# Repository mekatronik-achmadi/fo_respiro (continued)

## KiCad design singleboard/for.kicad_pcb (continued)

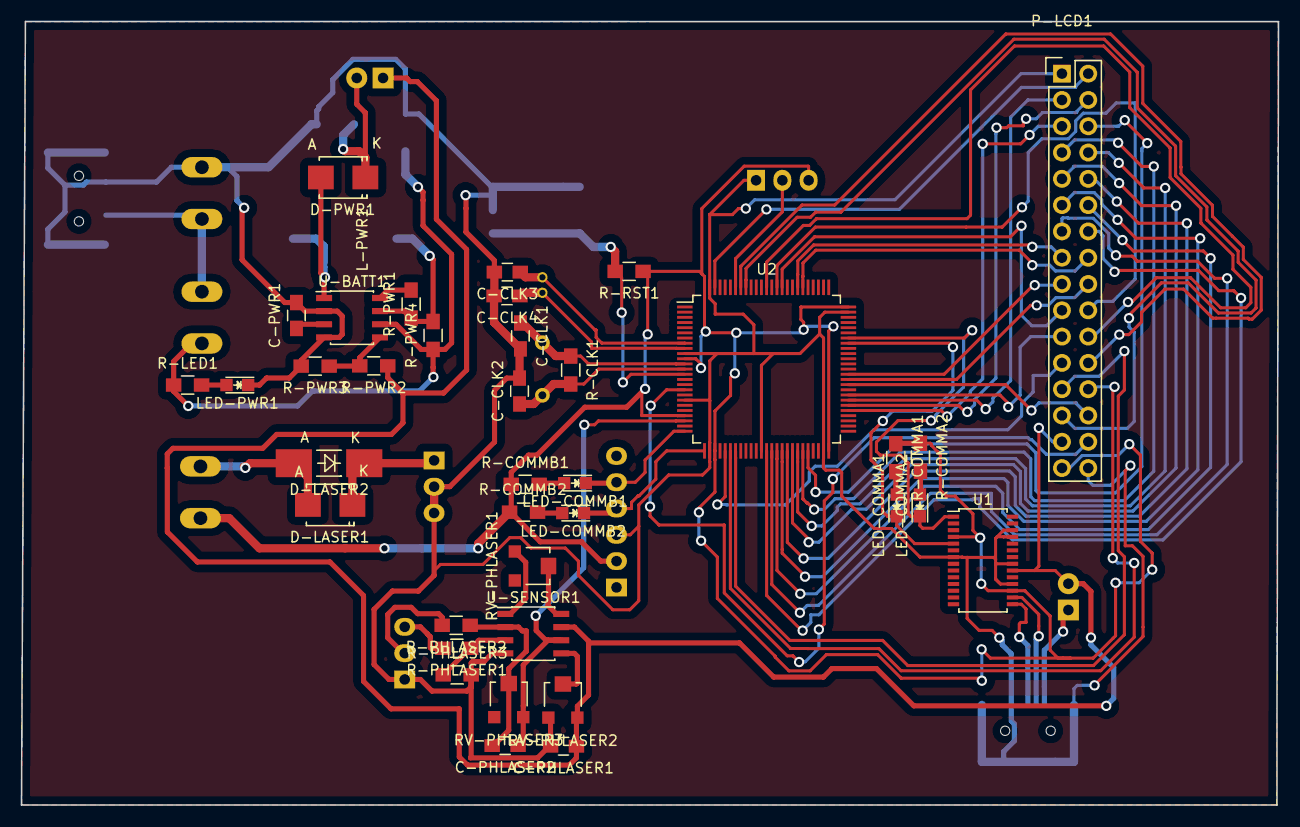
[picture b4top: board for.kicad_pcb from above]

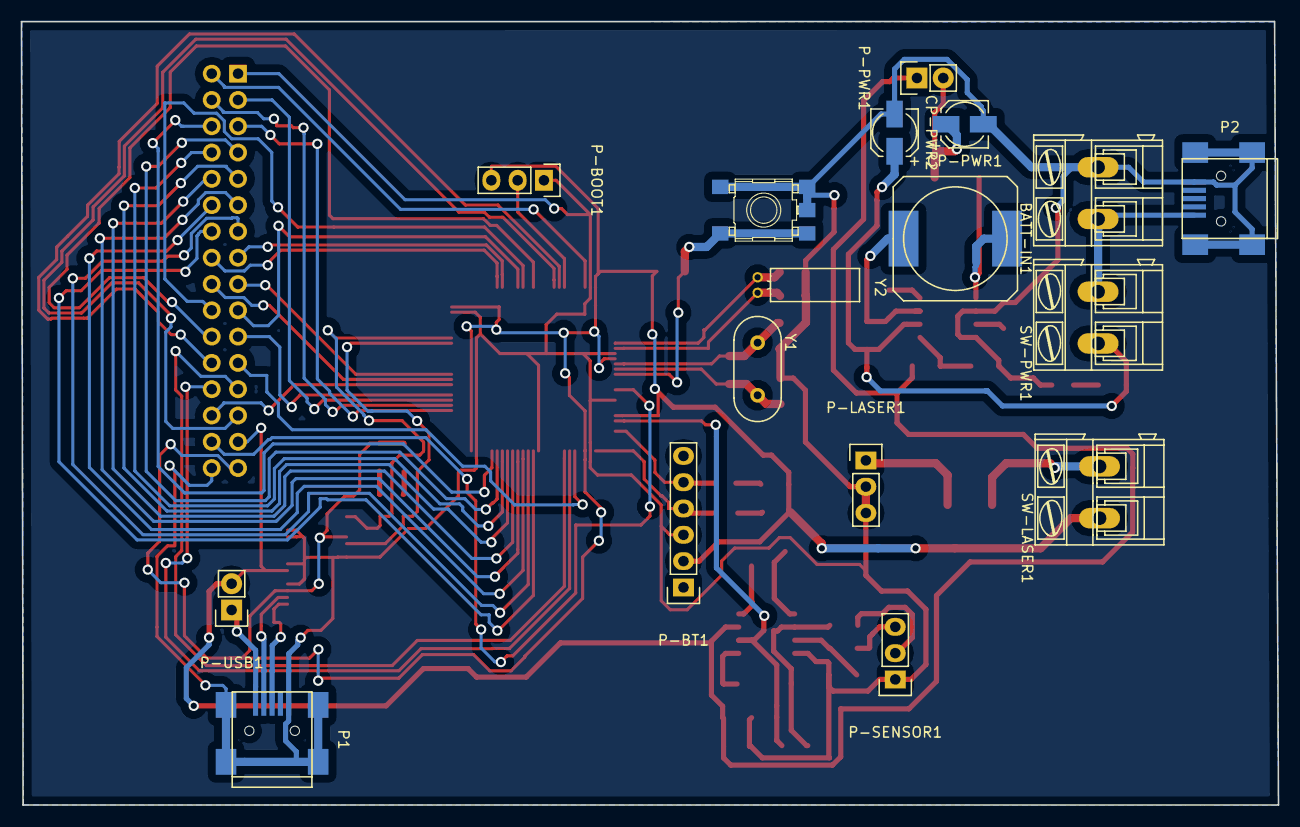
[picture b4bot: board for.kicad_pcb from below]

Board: 2 copper layers, 121.4 x 75.7 mm, 54 parts (17 on the bottom side), 67 nets.

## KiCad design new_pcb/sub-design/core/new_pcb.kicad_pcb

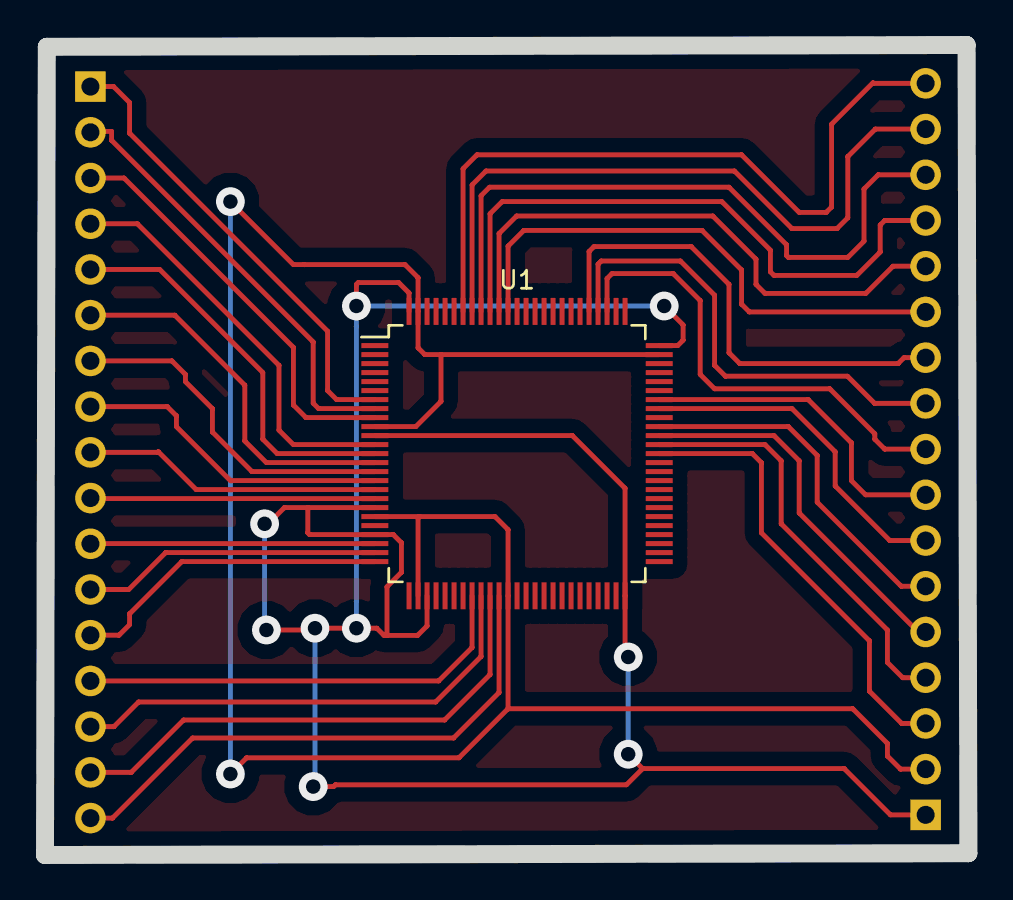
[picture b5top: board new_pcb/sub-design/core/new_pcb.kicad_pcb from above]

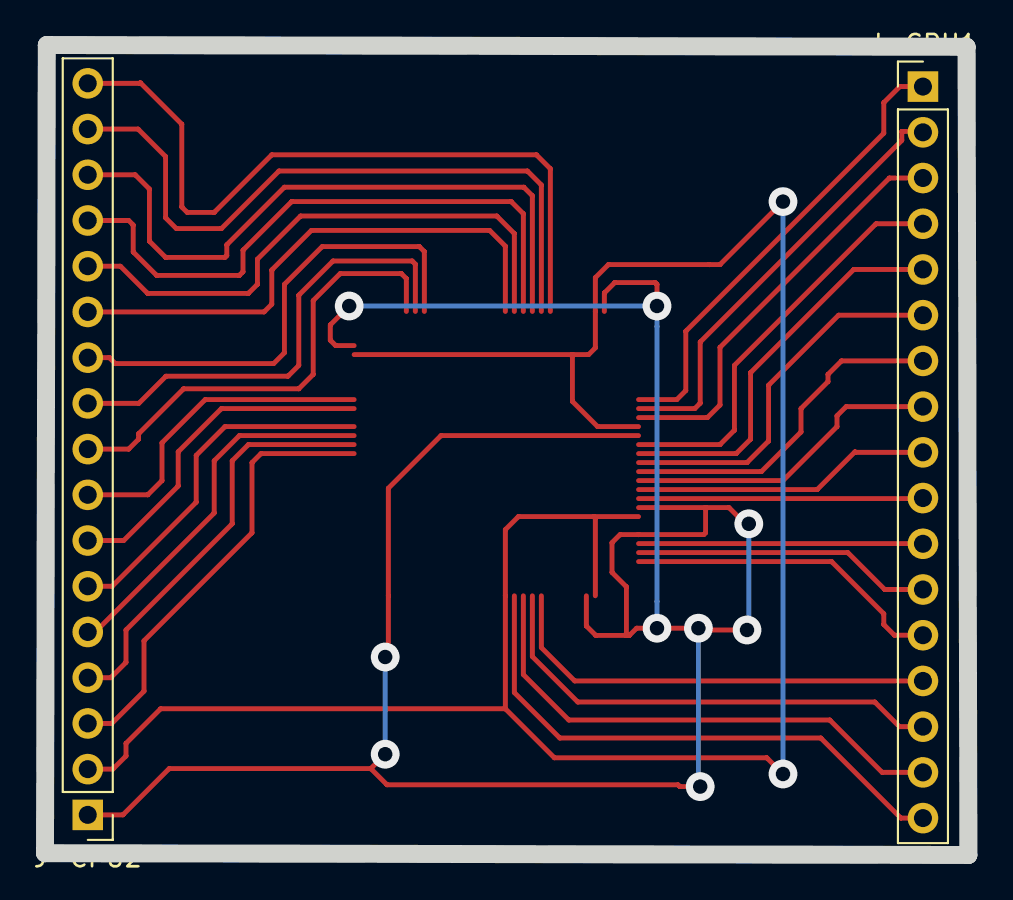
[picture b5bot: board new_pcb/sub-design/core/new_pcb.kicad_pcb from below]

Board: 2 copper layers, 51.3 x 45.0 mm, 3 parts (2 on the bottom side), 34 nets.

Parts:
J-CPU1, J-CPU2: CONN_01X17; Pin_Header_Straight_1x17_Pitch2.54mm
U1: STM32F407VGTx; LQFP-100_14x14mm_Pitch0.5mm

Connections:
/ADC_0: J-CPU1.11, U1.23
/ADC_1: J-CPU1.12, U1.24
/ADC_2: J-CPU1.13, U1.25
/ADC_EOC: J-CPU2.14, U1.91
/ADC_MCLK: J-CPU2.12, U1.89
/ADC_SCL: J-CPU2.15, U1.92
/ADC_SDA: J-CPU2.16, U1.93
/ADC_XCLR: J-CPU2.13, U1.90
/BOOT: J-CPU2.17, U1.94
/GLCD_0: J-CPU1.7, U1.15
/GLCD_1: J-CPU1.8, U1.16
/GLCD_2: J-CPU1.9, U1.17
/GLCD_3: J-CPU1.10, U1.18
/GLCD_4: J-CPU1.14, U1.33
/GLCD_5: J-CPU1.15, U1.34
/GLCD_6: J-CPU2.3, U1.63
/GLCD_7: J-CPU2.4, U1.64
/GLCD_CS1: J-CPU2.5, U1.65
/GLCD_CS2: J-CPU2.6, U1.66
/GLCD_EN: J-CPU1.1, U1.7
/GLCD_RS: J-CPU2.9, U1.78
/GLCD_RST: J-CPU2.11, U1.80
/GLCD_RW: J-CPU2.10, U1.79
/OSC24_IN: J-CPU1.4, U1.12
/OSC24_OUT: J-CPU1.5, U1.13
/OSC32_IN: J-CPU1.2, U1.8
/OSC32_OUT: J-CPU1.3, U1.9
/RST: J-CPU1.6, U1.14
/RX: J-CPU2.7, U1.68
/TX: J-CPU2.8, U1.69
/USER_INPUT_1: J-CPU1.16, U1.35
/USER_INPUT_2: J-CPU1.17, U1.36
GND: J-CPU2.2, U1.10, U1.20, U1.27, U1.37, U1.74, U1.99
VDD: J-CPU2.1, U1.11, U1.19, U1.22, U1.28, U1.50, U1.75, U1.100

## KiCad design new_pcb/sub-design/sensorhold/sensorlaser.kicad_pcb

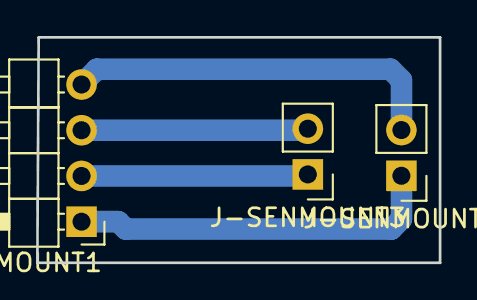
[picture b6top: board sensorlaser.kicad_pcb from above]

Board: 2 copper layers, 22.4 x 12.5 mm, 3 parts (0 on the bottom side), 4 nets.

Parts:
J-SENMOUNT1: CONN_01X04; Pin_Header_Angled_1x04_Pitch2.54mm
J-SENMOUNT2, J-SENMOUNT3: CONN_01X02; Pin_Header_Straight_1x02_Pitch2.54mm

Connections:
/IN+: J-SENMOUNT1.3, J-SENMOUNT3.2
/IN-: J-SENMOUNT1.2, J-SENMOUNT3.1
/VSEN+: J-SENMOUNT1.1, J-SENMOUNT2.1
/VSEN-: J-SENMOUNT1.4, J-SENMOUNT2.2

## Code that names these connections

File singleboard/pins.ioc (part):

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Mcu.Name=STM32F103V(C-D-E)Tx
Mcu.Package=LQFP100
Mcu.UserName=STM32F103VETx
PA0-WKUP.Signal=ADCx_IN0
PA2.Mode=Asynchronous
PA2.Signal=USART2_TX
PA3.Mode=Asynchronous
PA3.Signal=USART2_RX
PA5.Signal=GPIO_Output
PA6.Signal=GPIO_Output
PA7.Signal=GPIO_Output
PB6.Signal=GPIO_Output
PB7.Signal=GPIO_Output
PC12.Signal=GPIO_Output
PC14-OSC32_IN.Signal=RCC_OSC32_IN
PC15-OSC32_OUT.Signal=RCC_OSC32_OUT
PD0.Signal=GPIO_Output
PD1.Signal=GPIO_Output
PD10.Signal=GPIO_Output
PD11.Signal=GPIO_Output
PD13.Signal=GPIO_Output
PD14.Signal=GPIO_Output
PD15.Signal=GPIO_Output
PD4.Signal=GPIO_Output
PD5.Signal=GPIO_Output
PD7.Signal=GPIO_Output
PD8.Signal=GPIO_Output
PD9.Signal=GPIO_Output
PE1.Signal=GPIO_Output
PE10.Signal=GPIO_Output
PE11.Signal=GPIO_Output
PE12.Signal=GPIO_Output
PE13.Signal=GPIO_Output
PE14.Signal=GPIO_Output
PE15.Signal=GPIO_Output
PE7.Signal=GPIO_Output
PE8.Signal=GPIO_Output
PE9.Signal=GPIO_Output

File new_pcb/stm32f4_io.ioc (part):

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Mcu.Name=STM32F407V(E-G)Tx
Mcu.Package=LQFP100
Mcu.UserName=STM32F407VGTx
PA0-WKUP.Signal=ADCx_IN0
PA1.Signal=ADCx_IN1
PA10.Signal=USART1_RX
PA2.Signal=ADCx_IN2
PA9.Signal=USART1_TX
PB0.Signal=GPIO_Input
PB1.Signal=GPIO_Input
PB2.Signal=EVENTOUT
PB3.Signal=S_TIM2_CH2
PB4.Signal=GPIO_Output
PB5.Signal=GPXTI5
PB6.Mode=I2C
PB6.Signal=I2C1_SCL
PB7.Mode=I2C
PB7.Signal=I2C1_SDA
PC0.Signal=GPIO_Output
PC1.Signal=GPIO_Output
PC10.Signal=GPIO_Output
PC11.Signal=GPIO_Output
PC12.Signal=GPIO_Output
PC13-ANTI_TAMP.Signal=GPIO_Output
PC14-OSC32_IN.Signal=RCC_OSC32_IN
PC15-OSC32_OUT.Signal=RCC_OSC32_OUT
PC2.Signal=GPIO_Output
PC3.Signal=GPIO_Output
PC4.Signal=GPIO_Output
PC5.Signal=GPIO_Output
PC6.Signal=GPIO_Output
PC7.Signal=GPIO_Output
PC8.Signal=GPIO_Output
PC9.Signal=GPIO_Output
PH0-OSC_IN.Signal=RCC_OSC_IN
PH1-OSC_OUT.Signal=RCC_OSC_OUT
RCC.HSE_VALUE=25000000
RCC.SYSCLKFreq_VALUE=16000000

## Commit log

2017-01-30 pcb route start
2017-02-01 PCB Progress
2017-02-01 PCB done
2017-02-01 initial firmware
2017-02-01 3d model
2017-02-01 all 3D on PCB done
2017-02-01 pcb lcd done
2017-02-01 pcb all done
2017-02-01 model box 3d
2017-02-02 model 3d
2017-02-02 box 3d
2017-02-02 model 3d done
2017-02-08 preview_prototype
2017-03-22 grafik
2017-03-22 graph
2017-10-03 re-working
2017-10-05 new design
2017-10-11 progress
2017-10-13 progres hardware oke
2017-10-15 serial run (chibios30)
2017-10-15 pisah directory
2017-10-15 GLCD Text shown
2017-10-15 stm32 ks0108 non-ugfx
2017-10-15 glcd progress: show bitmap
2017-10-15 GLCD progres: basic draw
2017-10-16 glcd text data
2017-10-17 base system OK
2017-10-17 ADC always on full
2017-10-17 solusi ADC VREF+
2017-10-18 Grafik Jalan
2017-10-29 laser only
2017-11-02 thorlab sensor addon
2018-09-18 report
2018-09-20 report html
2018-10-02 old project re-foldered
2018-10-02 plan_report
2018-10-02 new miniSTM32F103V fork
2018-10-02 library path
2018-10-02 graph pre
2018-10-02 refresh rate at 500ms
2018-10-02 display demo ok
2018-10-03 gui oke
2018-10-03 ADC API
2018-10-03 try display ADC
2018-10-03 ADC data source
2018-10-03 try ADC feed
2018-10-03 ADC belum tampil
2018-10-05 ADC Graph
2018-10-05 ADC autorun OK
2018-10-09 android section
2018-10-09 android license
2018-10-09 android graphlib
2018-10-10 use single ADC
2018-10-10 start bt log
2018-10-10 BT sending ok
2018-10-11 stm32 broadcast adc data
2018-10-11 start bluetooth interfacing
2018-10-11 Android BT examples
2018-10-11 Android HC-05 Terminal works
2018-10-12 progress bluetooth interfacing
2018-10-13 use official ugfx 2.8
2018-10-14 bluetooth cmd routine
2018-10-14 shell no any local echo
2018-10-14 bluetooth reply request
2018-10-18 progres apk
2018-10-18 tinggal data kalibrasi
2018-10-18 progres
2018-10-19 calibration work on uW (not nW)
2018-10-25 usb distributor
2018-10-25 technical document
2018-10-30 doxygen document related
2018-10-30 doxygen documentation
2018-10-30 doxygen api command deprecated
2018-10-30 doxygen
2018-10-30 doxygen documentation oke
2018-10-30 progres technical document
2018-10-30 doxygen document
2018-10-30 tex document
2018-10-30 document
2019-01-06 last progress
2019-01-20 tambah permission
2020-05-04 update progres
2020-05-04 development
2020-05-05 drop axis
2020-05-05 try to use new ugfx
2020-05-05 drop memory usage
2020-05-06 prototype counter
2020-05-07 update run
2020-05-31 improve frequency using input capture
2020-05-31 test to real sensor
2020-05-31 data process moved to GPT
2020-05-31 at least working as expected
2020-05-31 timing seems fine
2020-06-01 add more doxygen from previous progress
2020-06-01 update doxygen config
2020-06-01 words can hurt
2020-06-01 doxygen threads as functions
2020-06-01 Official name is FO Respiro Metri DAQ
2020-06-14 need more improvement?
2020-06-20 controlled environemt OK
2020-06-20 simple custom OLS
2020-06-21 start work on MMC
2020-06-21 drop MMC support
2020-06-22 serial data
2020-06-22 improve run/stop via serial
2020-07-05 real data out
2020-08-14 serial comm interface
2020-08-18 update interface
2020-08-18 serial interface
